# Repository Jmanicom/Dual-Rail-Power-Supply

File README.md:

# Dual-Rail-Power-Supply
A low-noise power supply designed around the usage with audio circuits and low power applications. This power supply,
once polished, will hopefully be used for a audio devlopment board I have in the works.

### **Skills Used for Project**
***Analog Circuit Design, KiCad, LTSPICE, Hand/Hot Air Soldering, Component Selection, Oscilloscope, Testing/Validation***

---

# Design (V1.0.0)
The power Supply is based around Analog Devices **MAX17577/8+**, along with their low-noise linear regulators, the **ADP7182** and **ADP7102**.
I chose these components as it was my first approach at designing such a project, and these components were easy to work with and could
be simulated using **LTSPICE**. The board featues a USB-C 3.0 Female Port for power input where a USB PD chip (**CH221K**) communicates with
PD compatible devices to negotiate power delivery. The device is desgined to negotiate for 9V DC from the USB-C port, and delivers that to
the switiching DC-DC inverter and the linear positive regulator.

The board comes with 3 indicator LED's to let the user know the status of the various power rails (9V In, -6V, +6V). Additionally, because this
board is a work in progress prototype, I have opted for header pins as the output ports to supply power output for testing. Furthermore, there are
testpoint pads located where important signals come from so low-interference testing can be preformed.

## MAX17577/8+
The **MAX17577/8** are a series of high efficiency, synchronous switching DC-DC inverted converters. This chip is able to produce anywhere from -4.5V
to -60V DC. For this project, I have opted for the **MAX17578** for its DCM (Discontinuous Conduction Mode) as DCM converters tend to preform better
in transient responses, and in lighter loads. However, the drawback from this approach is potential additional EMI (Electromagentic Interference). The
PCB was designed with this is mind as I tried to place this converter as far from the linear regulators as I could, along with the noisiest part, the inductor.

The converter takes a 9V input and is configured using a resistor divider to output -6V at roughly 0.8A max. This output is slighly choppy at times,
so it is then fed into a linear regulator (**ADP7182**) where it can then be smoothed out

## ADP7182/02
To provide stable and low-noise power rails, I opted for the **ADP7182/02** for the negative rail and positive rail respectively. The dropoff voltage is
relatively low, and thus I found the associated power loss from these chips to be small. Each chip is limited to 200mA, which is suitable for the application
in mind. Additionally, to help stabilize rails and reduce noise, input and output capacitors have been added for each regulator in values of 10uf, and 2.2uf.
This choice was suggested by Analog Devices datasheets for each device, along with a group of series capacitors in parallel with the feedback resistors at
a value of 220pf.

# Simulation

# Testing

# Notes

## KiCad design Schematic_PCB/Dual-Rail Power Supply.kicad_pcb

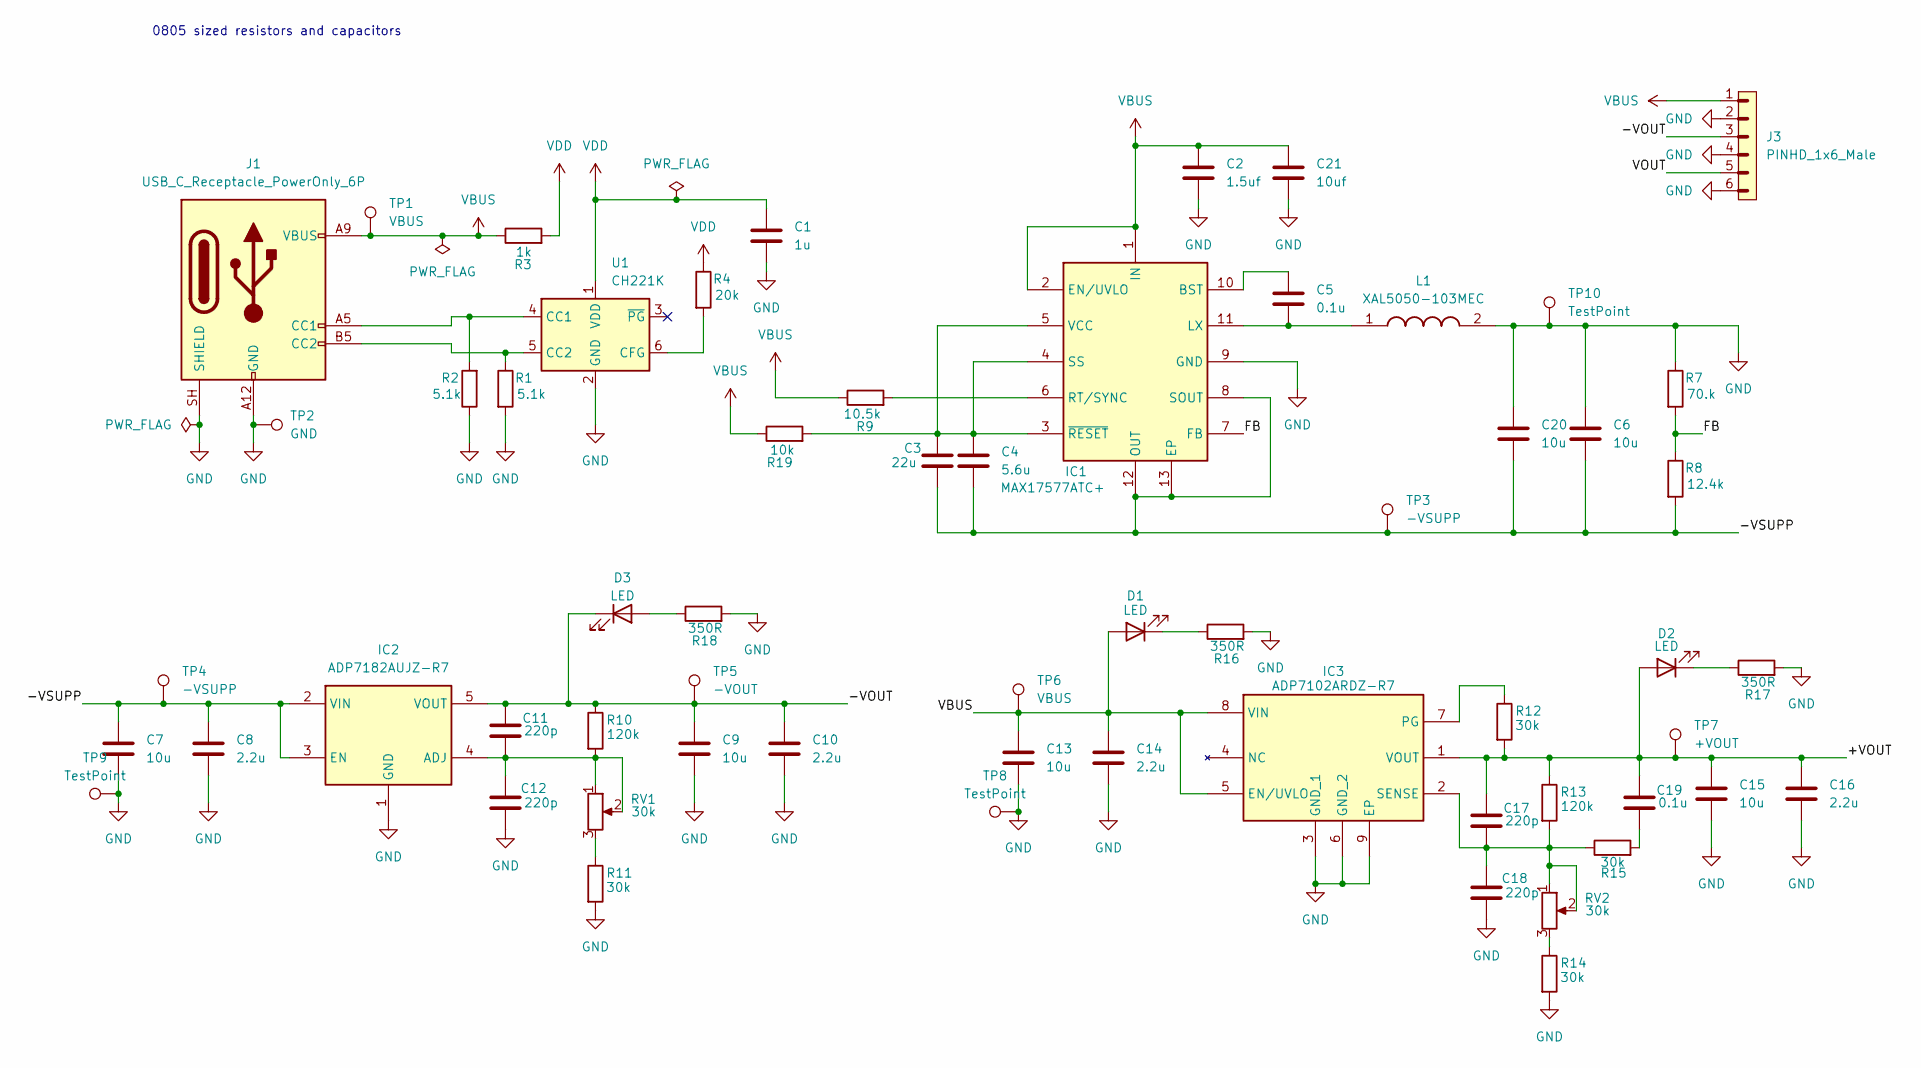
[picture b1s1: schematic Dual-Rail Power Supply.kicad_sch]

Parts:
C1: 1u; C_0805_2012Metric_Pad1.18x1.45mm_HandSolder
C2: 1.5uf; C_0805_2012Metric_Pad1.18x1.45mm_HandSolder
C3: 22u; C_0805_2012Metric_Pad1.18x1.45mm_HandSolder
C4: 5.6u; C_0805_2012Metric_Pad1.18x1.45mm_HandSolder
C5, C19: 0.1u; C_0603_1608Metric_Pad1.08x0.95mm_HandSolder
C6, C7, C9, C13, C15, C20: 10u; C_1206_3216Metric_Pad1.33x1.80mm_HandSolder
C8, C10, C14, C16: 2.2u; C_0805_2012Metric_Pad1.18x1.45mm_HandSolder
C11, C12, C17, C18: 220p; C_0603_1608Metric_Pad1.08x0.95mm_HandSolder
C21: 10uf; C_0805_2012Metric_Pad1.18x1.45mm_HandSolder
D1, D2, D3: LED; D_0805_2012Metric_Pad1.15x1.40mm_HandSolder
IC1: MAX17577ATC+; Manufacturer_Part_Number MAX17577ATC+; Mouser Part Number 700-MAX17577ATC+
IC2: ADP7182AUJZ-R7; Manufacturer_Part_Number ADP7182AUJZ-R7; Mouser Part Number 584-ADP7182AUJZ-R7
IC3: ADP7102ARDZ-R7; Manufacturer_Part_Number ADP7102ARDZ-R7; Mouser Part Number 584-ADP7102ARDZ-R7
J1: USB_C_Receptacle_PowerOnly_6P; USB_C_Receptacle_GCT_USB4135-GF-A_6P_TopMnt_Horizontal
J3: PINHD_1x6_Male; PinHeader_1x06_P2.54mm_Vertical
L1: XAL5050-103MEC; XEL5050-103MEC; Manufacturer_Part_Number XAL5050-103MEC; Mouser Part Number 994-XAL5050-103MEC
R1, R2: 5.1k; R_0805_2012Metric_Pad1.20x1.40mm_HandSolder
R3: 1k; R_0805_2012Metric_Pad1.20x1.40mm_HandSolder
R4: 20k; R_0805_2012Metric_Pad1.20x1.40mm_HandSolder
R7: 70.k; R_0805_2012Metric_Pad1.20x1.40mm_HandSolder
R8: 12.4k; R_0805_2012Metric_Pad1.20x1.40mm_HandSolder
R9: 10.5k; R_0805_2012Metric_Pad1.20x1.40mm_HandSolder
R10, R13: 120k; R_0805_2012Metric_Pad1.20x1.40mm_HandSolder
R11, R12, R14, R15: 30k; R_0805_2012Metric_Pad1.20x1.40mm_HandSolder
R16, R17, R18: 350R; R_0805_2012Metric_Pad1.20x1.40mm_HandSolder
R19: 10k; R_0805_2012Metric_Pad1.20x1.40mm_HandSolder
RV1, RV2: 30k; Potentiometer_Bourns_TC33X_Vertical
TP1, TP6: VBUS; TestPoint_Pad_D1.5mm
TP2: GND; TestPoint_Pad_D1.5mm
TP3, TP4: -VSUPP; TestPoint_Pad_D1.5mm
TP5: -VOUT; TestPoint_Pad_D1.5mm
TP7: +VOUT; TestPoint_Pad_D1.5mm
TP8, TP9, TP10: TestPoint; TestPoint_Pad_D1.5mm
U1: CH221K; SOT-23-6

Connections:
/+VOUT: C15.1, C16.1, C17.1, C19.1, D2.2 (A), IC3.1 (VOUT), R12.2, R13.1, TP7.1 (1_1)
/-VOUT: C9.1, C10.1, C11.1, D3.1 (K), IC2.5 (VOUT), J3.3, R10.1, TP5.1 (1_1)
/-VSUPP: C3.2, C4.2, C6.2, C7.1, C8.1, C20.2, IC1.8 (SOUT), IC1.12 (OUT), IC1.13 (EP), IC2.2 (VIN), IC2.3 (EN), R8.2, TP3.1 (1_1), TP4.1 (1_1)
/FB: IC1.7 (FB), R7.2, R8.1
/VOUT: J3.5
GND: C1.2, C2.2, C6.1, C7.2, C8.2, C9.2, C10.2, C12.2, C13.2, C14.2, C15.2, C16.2, C18.2, C20.1, C21.2, IC1.9 (GND), IC2.1 (GND), IC3.3 (GND_1), IC3.6 (GND_2), IC3.9 (EP), J1.A12 (GND), J1.B12 (GND), J1.SH (SHIELD), J3.2, J3.4, J3.6, L1.2, R1.2, R2.1, R7.1, R11.2, R14.2, R16.2, R17.2, R18.2, TP2.1 (1_1), TP8.1 (1_1), TP9.1 (1_1), TP10.1 (1_1), U1.2 (GND)
unnamed: C19.2, R15.2
unnamed: D1.1 (K), R16.1
unnamed: D2.1 (K), R17.1
unnamed: D3.2 (A), R18.1
unnamed: C5.1, IC1.10 (BST)
unnamed: C5.2, IC1.11 (LX), L1.1
unnamed: IC1.6 (RT/SYNC), R9.2
unnamed: C3.1, C4.1, IC1.3 (~RESET), IC1.4 (SS), IC1.5 (VCC), R19.2
unnamed: C11.2, C12.1, IC2.4 (ADJ), R10.2, RV1.1, RV1.2
unnamed: IC3.7 (PG), R12.1
unnamed: C17.2, C18.1, IC3.2 (SENSE), R13.2, R15.1, RV2.1, RV2.2
unnamed: J1.A5 (CC1), R2.2, U1.4 (CC1)
unnamed: J1.B5 (CC2), R1.1, U1.5 (CC2)
unnamed: R11.1, RV1.3
unnamed: R14.1, RV2.3
unnamed: R4.2, U1.6 (CFG)
VBUS: C2.1, C13.1, C14.1, C21.1, D1.2 (A), IC1.1 (IN), IC1.2 (EN/UVLO), IC3.5 (EN/UVLO), IC3.8 (VIN), J1.A9 (VBUS), J1.B9 (VBUS), J3.1, R3.1, R9.1, R19.1, TP1.1 (1_1), TP6.1 (1_1)
VDD: C1.1, R3.2, R4.1, U1.1 (VDD)

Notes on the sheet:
0805 sized resistors and capacitors

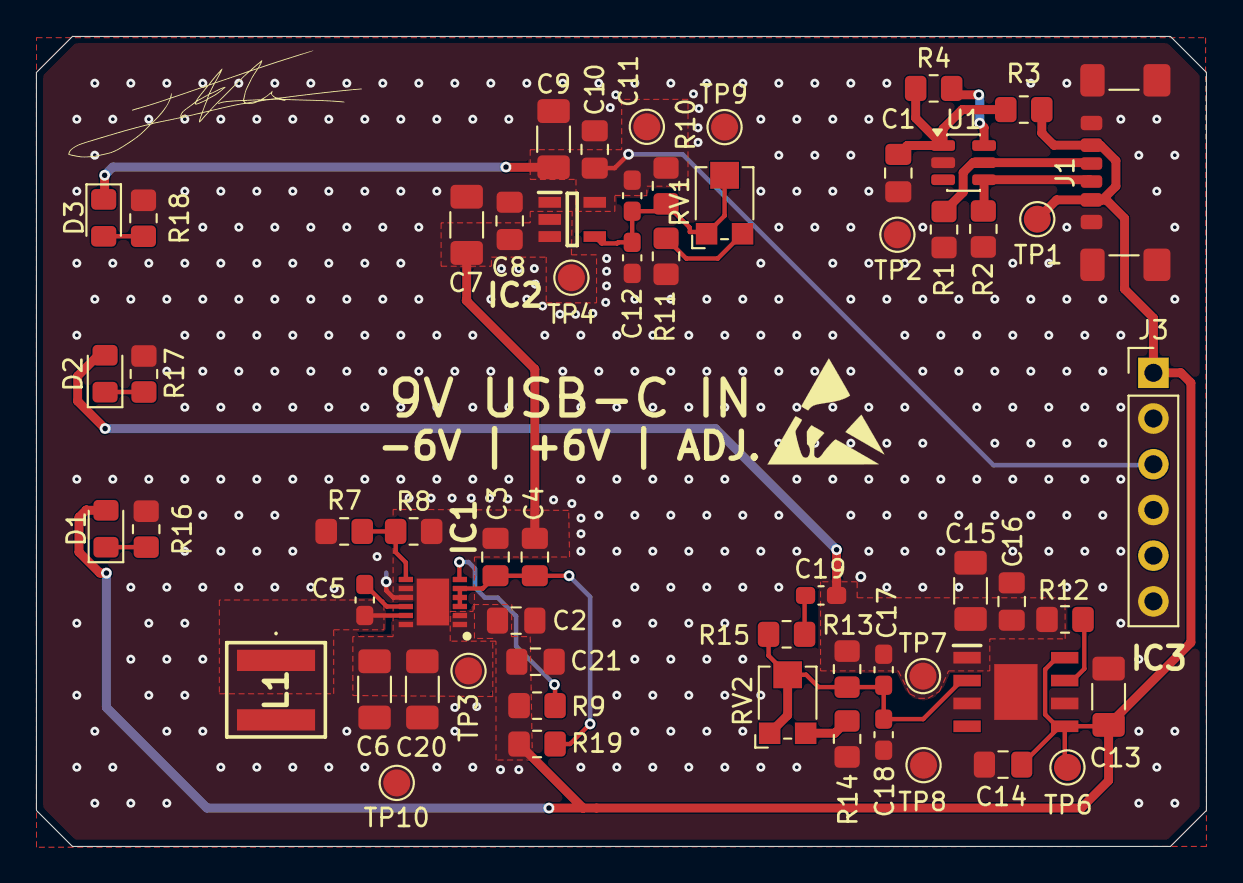
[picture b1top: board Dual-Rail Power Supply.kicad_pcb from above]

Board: 4 copper layers, 65.0 x 45.0 mm, 60 parts (0 on the bottom side), 23 nets.
